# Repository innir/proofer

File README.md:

# Temperature control with timer for a homemade proofing box

## BOM

- LOLIN D1 mini (Pro)
- SSR RP1A23D5
- Power supply IRM-05-5
- Resistor 4.7 kOhm
- Terminal WAGO 250-202
- Terminal WAGO 250-203
- Housing GEH KSW 50 (G086)
- Temperature sensor DS18B20

- Heating cable / mat, 230V, ~20W
- Insulation box

## LICENSE

The project is licensed under the GNU LESSER GENERAL PUBLIC LICENSE 2.1. Files in the folder `kicad` are licensed under the Creative Commons Attribution-ShareAlike 4.0 International License (CC BY-SA). Files in the folder `kicad/snapeda-libraries` are provided by [SnapEDA](https://www.snapeda.com) and are licensed under the Creative Commons Attribution-ShareAlike 4.0 International License (CC BY-SA) with the [Design Exception 1.0](https://www.snapeda.com/about/FAQ/#designexception).

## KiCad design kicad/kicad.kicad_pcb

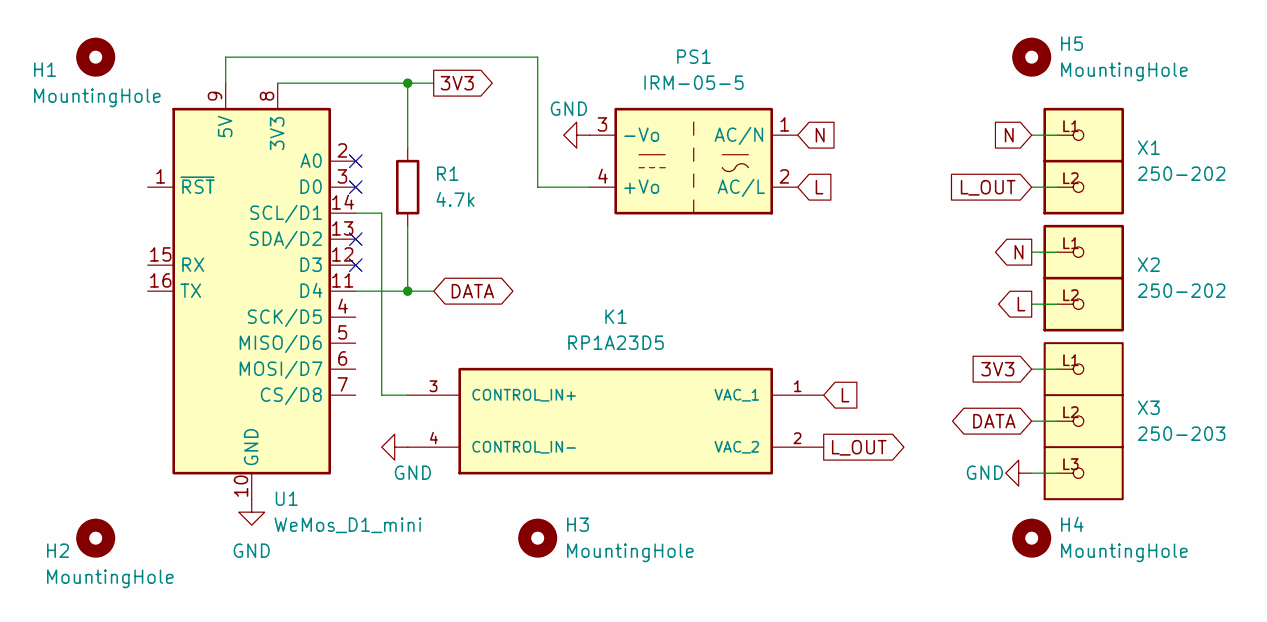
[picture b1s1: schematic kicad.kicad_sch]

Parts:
H1, H2, H3, H4, H5: MountingHole; MountingHole_2.7mm_M2.5
K1: RP1A23D5; RELAY_RP1A23D5; PARTREV 30/08/2021
PS1: IRM-05-5; Converter_ACDC_MeanWell_IRM-05-xx_THT
R1: 4.7k; R_Axial_DIN0207_L6.3mm_D2.5mm_P10.16mm_Horizontal
U1: WeMos_D1_mini; WEMOS_D1_mini_light
X1, X2: 250-202; P-250-202
X3: 250-203; P-250-203

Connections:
3V3: R1.1, U1.8 (3V3), X3.L1
DATA: R1.2, U1.11 (D4), X3.L2
GND: K1.4 (CONTROL_IN-), PS1.3 (-Vo), U1.10 (GND), X3.L3
L: K1.1 (VAC_1), PS1.2 (AC/L), X2.L2
L_OUT: K1.2 (VAC_2), X1.L2
N: PS1.1 (AC/N), X1.L1, X2.L1
unnamed: K1.3 (CONTROL_IN+), U1.14 (SCL/D1)
unnamed: PS1.4 (+Vo), U1.9 (5V)

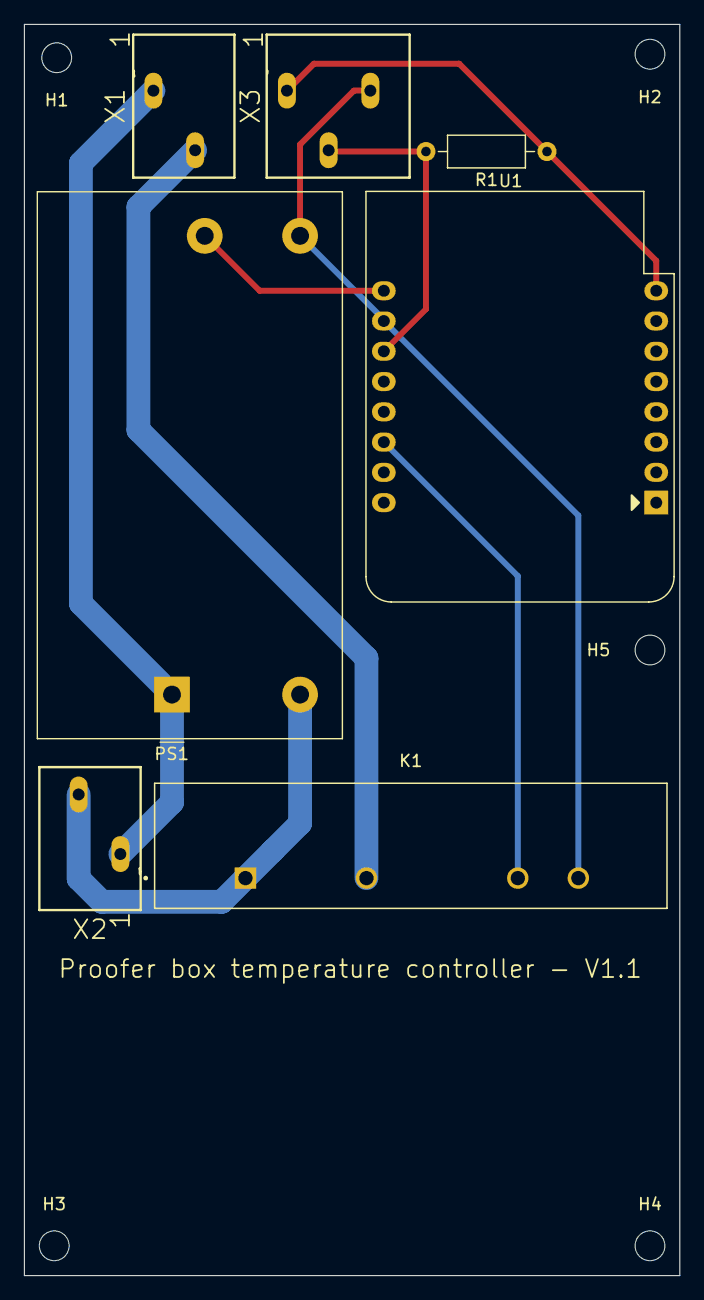
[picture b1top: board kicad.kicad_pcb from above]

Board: 2 copper layers, 55.0 x 105.0 mm, 12 parts (0 on the bottom side), 8 nets.

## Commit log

2023-01-24 First version of Proofer
2023-01-28 Make time zone configurable
2023-01-30 Add timer to set proofing end
2023-01-31 Change flash split to make OTA updates possible
2023-02-03 Use offset instead of alowance to control temperature
2023-02-03 Use correct unsigned integer type
2023-02-04 Add schematic, footprint and a short readme
2023-02-10 Ignore some kicad cache files
2023-02-12 Small schematic & footprint cleanups
2023-02-14 WIP: some more schematic & footprint updates
2024-01-03 Fix highcharts.js version
2024-01-03 Add LOLIN C3 mini as environment
